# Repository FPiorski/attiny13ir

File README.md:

# attiny13ir
#### Single button IR remote for triggering Canon DSLRs from 3d printers
Made this into a PCB only because I was playing with feeds and speeds for milling PCBs on my desktop CNC.

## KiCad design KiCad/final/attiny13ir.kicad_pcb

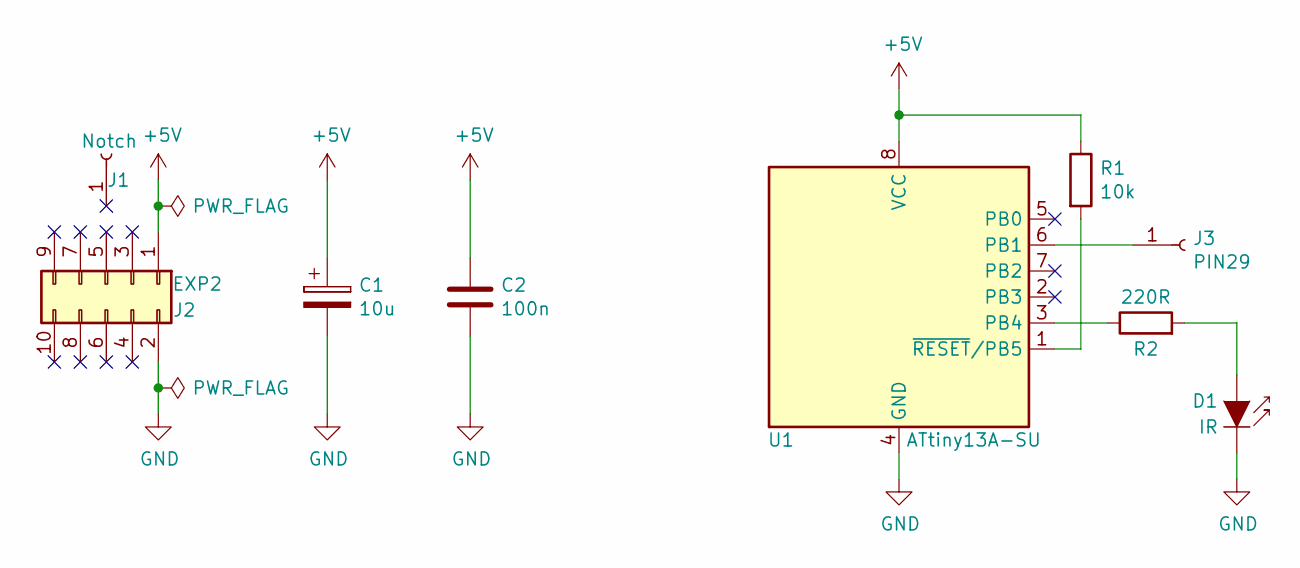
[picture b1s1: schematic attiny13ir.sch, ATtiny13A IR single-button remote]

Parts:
C1: 10u; C_0805_2012Metric_Pad1.15x1.40mm_HandSolder
C2: 100n; C_0805_2012Metric_Pad1.15x1.40mm_HandSolder
D1: IR; D_1812_4532Metric
J1: Notch; PinSocket_1x01_P2.54mm_Vertical
J2: EXP2; PinSocket_2x05_P2.54mm_Vertical
J3: PIN29; PinSocket_1x01_P2.54mm_Vertical
R1: 10k; R_0805_2012Metric_Pad1.15x1.40mm_HandSolder
R2: 220R; R_0805_2012Metric_Pad1.15x1.40mm_HandSolder
U1: ATtiny13A-SU; SOIJ-8_5.3x5.3mm_P1.27mm

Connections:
+5V: C1.1, C2.1, J2.1, R1.1, U1.8 (VCC)
GND: C1.2, C2.2, D1.1 (K), J2.2, U1.4 (GND)
unnamed: D1.2 (A), R2.2
unnamed: J3.1, U1.6 (PB1)
unnamed: R1.2, U1.1 (~RESET~/PB5)
unnamed: R2.1, U1.3 (PB4)

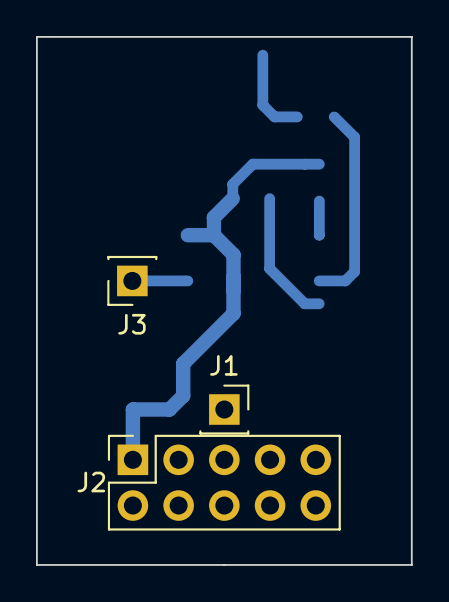
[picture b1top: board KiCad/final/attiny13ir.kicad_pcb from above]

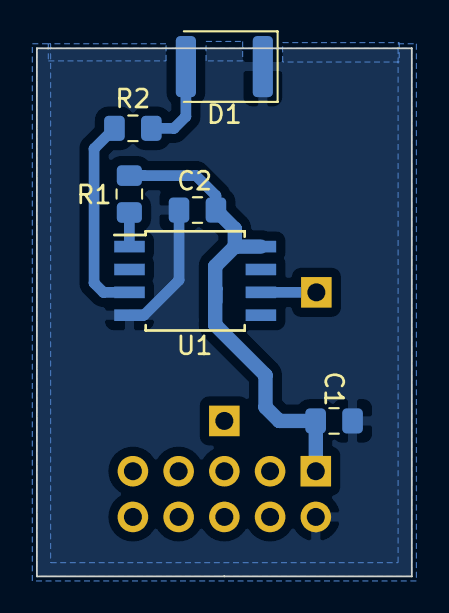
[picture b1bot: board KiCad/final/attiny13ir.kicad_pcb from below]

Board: 2 copper layers, 20.8 x 29.3 mm, 9 parts (6 on the bottom side), 6 nets.

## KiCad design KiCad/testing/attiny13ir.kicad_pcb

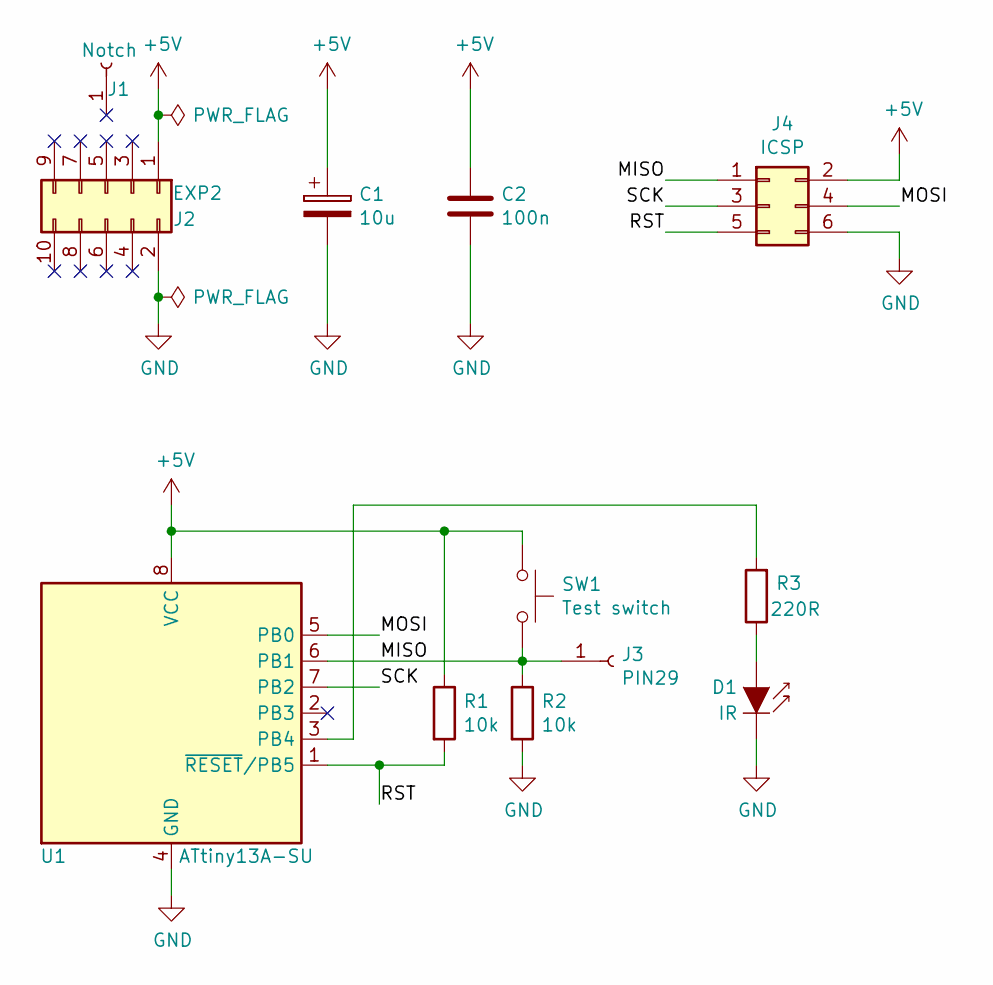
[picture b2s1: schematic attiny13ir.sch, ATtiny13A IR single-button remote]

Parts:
C1: 10u; C_Radial_D8.0mm_H11.5mm_P3.50mm
C2: 100n; C_0805_2012Metric_Pad1.15x1.40mm_HandSolder
D1: IR; D_1812_4532Metric
J1: Notch; PinSocket_1x01_P2.54mm_Vertical
J2: EXP2; PinSocket_2x05_P2.54mm_Vertical
J3: PIN29; PinSocket_1x01_P2.54mm_Vertical
J4: ICSP; PinHeader_2x03_P2.54mm_Vertical
R1, R2: 10k; R_0805_2012Metric_Pad1.15x1.40mm_HandSolder
R3: 220R; R_0805_2012Metric_Pad1.15x1.40mm_HandSolder
SW1: Test switch; SW_PUSH_6mm
U1: ATtiny13A-SU; SOIJ-8_5.3x5.3mm_P1.27mm

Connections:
+5V: C1.1, C2.1, J2.1, J4.2, R1.1, SW1.1, U1.8 (VCC)
/MISO: J3.1, J4.1, R2.1, SW1.2, U1.6 (PB1)
/MOSI: J4.4, U1.5 (PB0)
/RST: J4.5, R1.2, U1.1 (~RESET~/PB5)
/SCK: J4.3, U1.7 (PB2)
GND: C1.2, C2.2, D1.1 (K), J2.2, J4.6, R2.2, U1.4 (GND)
unnamed: D1.2 (A), R3.1
unnamed: R3.2, U1.3 (PB4)

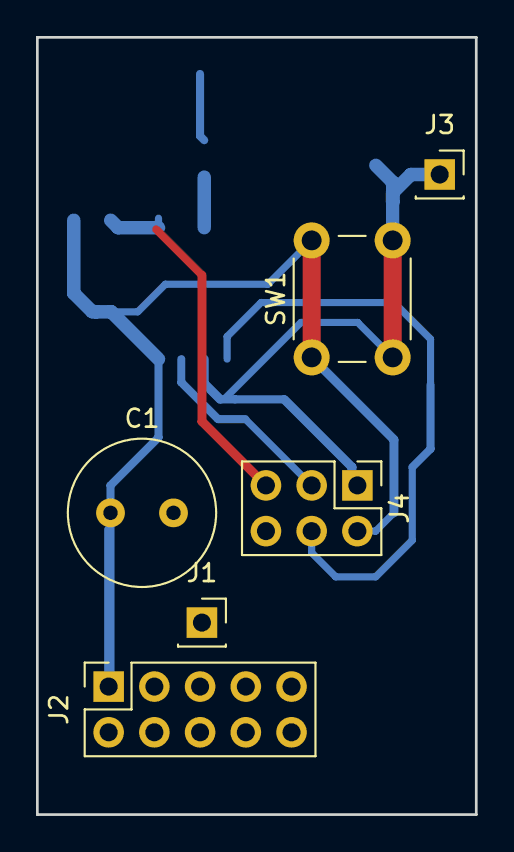
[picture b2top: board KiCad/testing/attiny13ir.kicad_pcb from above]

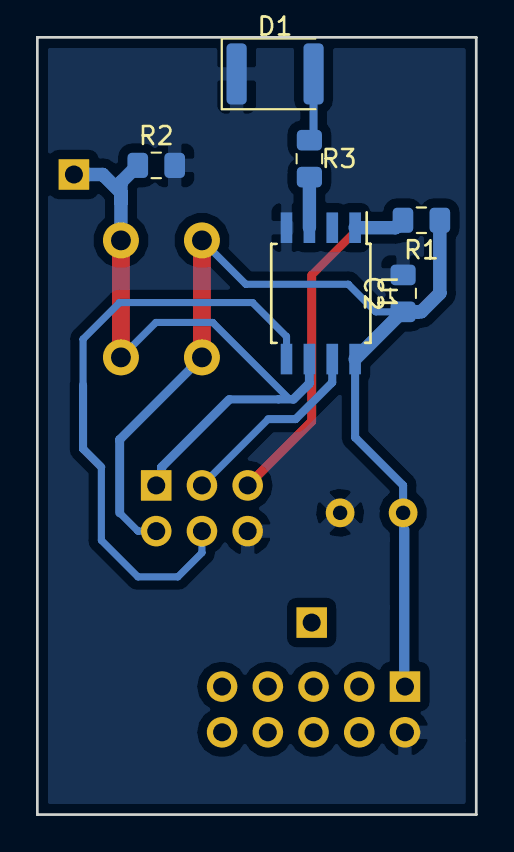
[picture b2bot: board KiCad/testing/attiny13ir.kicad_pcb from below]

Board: 2 copper layers, 24.4 x 43.2 mm, 12 parts (6 on the bottom side), 8 nets.

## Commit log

2020-09-25 minor fixes
